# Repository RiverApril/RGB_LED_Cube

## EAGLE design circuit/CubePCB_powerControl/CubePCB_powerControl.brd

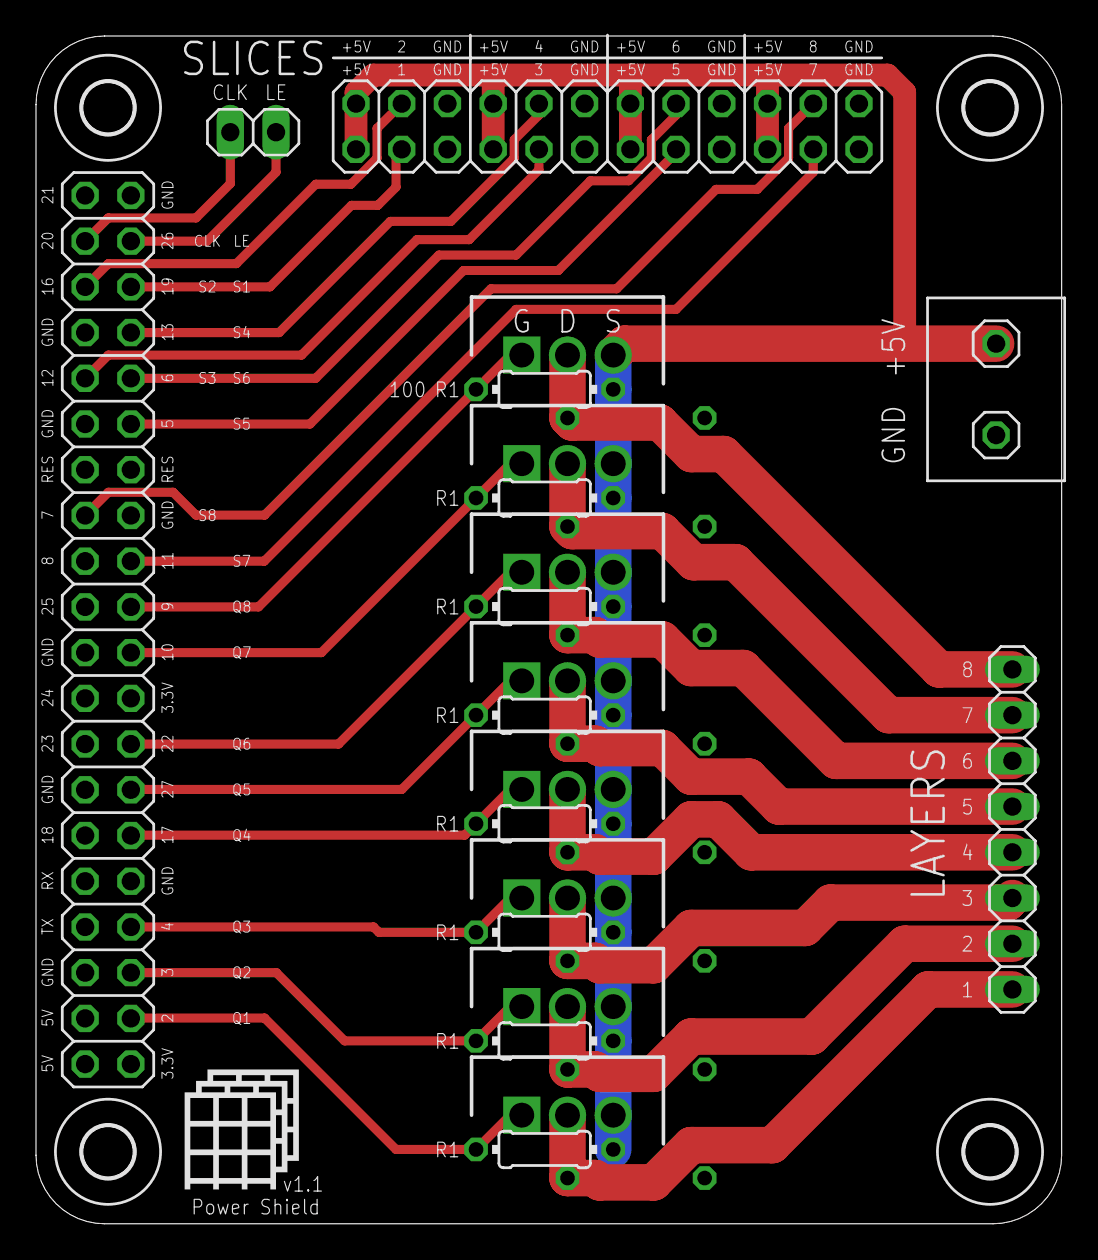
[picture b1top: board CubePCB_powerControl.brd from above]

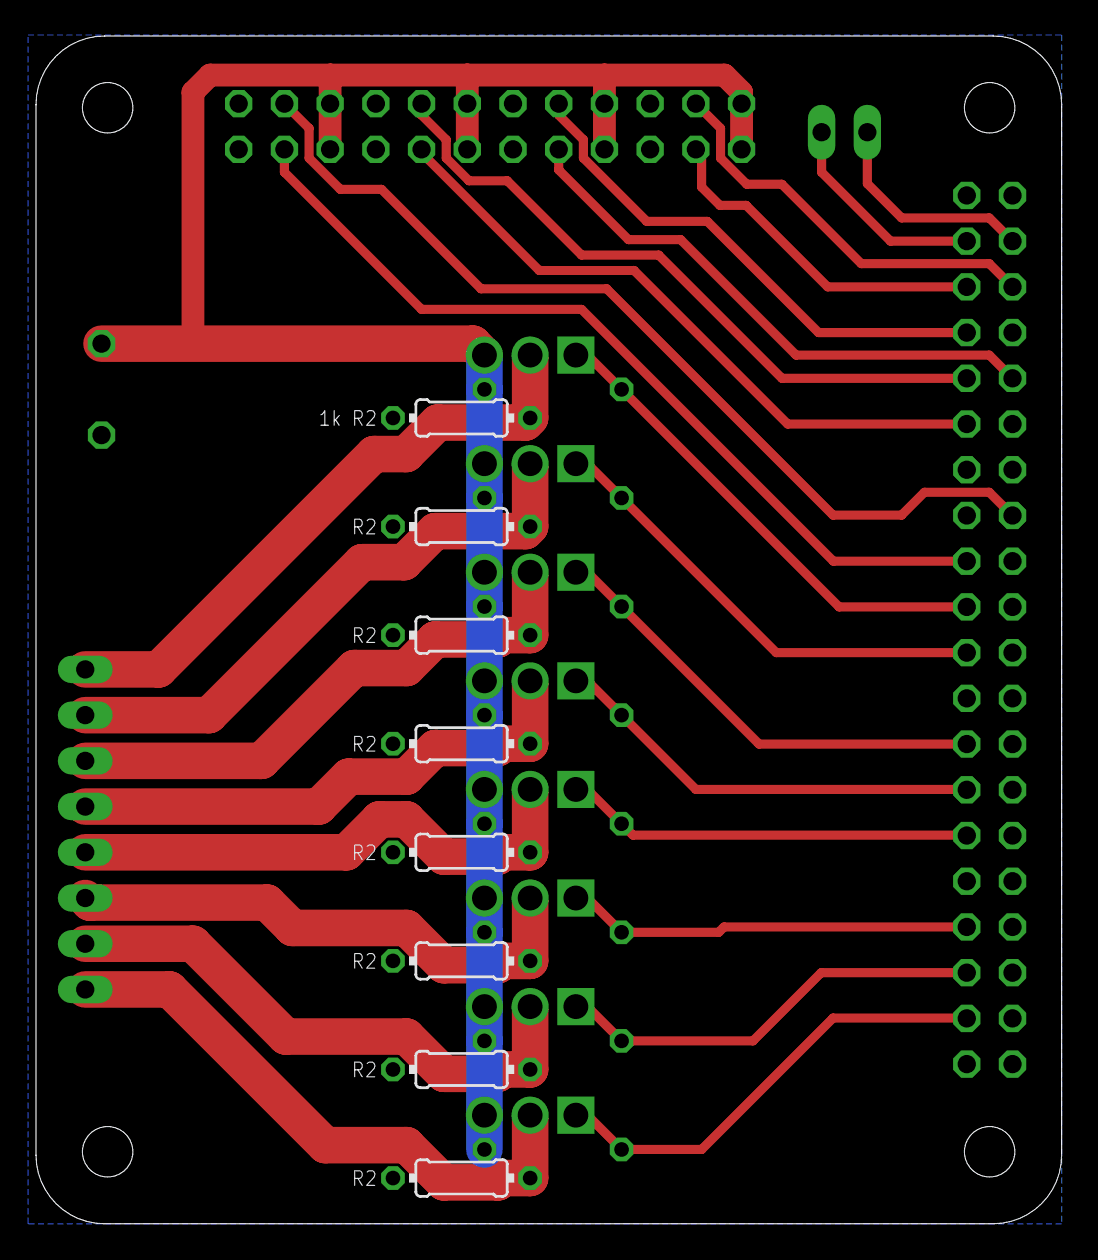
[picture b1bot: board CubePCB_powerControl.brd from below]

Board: 2 copper layers, 57.0 x 66.0 mm, 34 parts (8 on the bottom side), 28 nets.

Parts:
H5, H6, H7, H8: MOUNT-HOLE2.8; 2,8
JP1: 1X08
JP2, JP4: 1X01
JP5: 2X12
JP6: 1X02
LAYER1:Q1, LAYER2:Q1, LAYER3:Q1, LAYER4:Q1, LAYER5:Q1, LAYER6:Q1, LAYER7:Q1, LAYER8:Q1: AUIRF9Z34N; TO254P482X1016X2192-3P
LAYER1:R1, LAYER2:R1, LAYER3:R1, LAYER4:R1, LAYER5:R1, LAYER6:R1, LAYER7:R1, LAYER8:R1: 100; 0204/7
LAYER1:R2, LAYER2:R2, LAYER3:R2, LAYER4:R2, LAYER5:R2, LAYER6:R2, LAYER7:R2, LAYER8:R2: 1k; 0204/7
RASP_PI_GPIO: 2X20

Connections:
+5V: JP4.1, JP5.1, JP5.2, JP5.7, JP5.8, JP5.13, JP5.14, JP5.19, JP5.20, LAYER1:Q1.3, LAYER1:R2.1, LAYER2:Q1.3, LAYER2:R2.1, LAYER3:Q1.3, LAYER3:R2.1, LAYER4:Q1.3, LAYER4:R2.1, LAYER5:Q1.3, LAYER5:R2.1, LAYER6:Q1.3, LAYER6:R2.1, LAYER7:Q1.3, LAYER7:R2.1, LAYER8:Q1.3, LAYER8:R2.1
CLK: JP6.1, RASP_PI_GPIO.38
GND: JP2.1, JP5.5, JP5.6, JP5.11, JP5.12, JP5.17, JP5.18, JP5.23, JP5.24, LAYER1:R1.2, LAYER2:R1.2, LAYER3:R1.2, LAYER4:R1.2, LAYER5:R1.2, LAYER6:R1.2, LAYER7:R1.2, LAYER8:R1.2, RASP_PI_GPIO.9, RASP_PI_GPIO.25, RASP_PI_GPIO.39
L1: JP1.8, LAYER1:Q1.2, LAYER1:R1.1
L2: JP1.7, LAYER2:Q1.2, LAYER2:R1.1
L3: JP1.6, LAYER3:Q1.2, LAYER3:R1.1
L4: JP1.5, LAYER4:Q1.2, LAYER4:R1.1
L5: JP1.4, LAYER5:Q1.2, LAYER5:R1.1
L6: JP1.3, LAYER6:Q1.2, LAYER6:R1.1
L7: JP1.2, LAYER7:Q1.2, LAYER7:R1.1
L8: JP1.1, LAYER8:Q1.2, LAYER8:R1.1
LATCH: JP6.2, RASP_PI_GPIO.37
Q1: LAYER1:Q1.1, LAYER1:R2.2, RASP_PI_GPIO.3
Q2: LAYER2:Q1.1, LAYER2:R2.2, RASP_PI_GPIO.5
Q3: LAYER3:Q1.1, LAYER3:R2.2, RASP_PI_GPIO.7
Q4: LAYER4:Q1.1, LAYER4:R2.2, RASP_PI_GPIO.11
Q5: LAYER5:Q1.1, LAYER5:R2.2, RASP_PI_GPIO.13
Q6: LAYER6:Q1.1, LAYER6:R2.2, RASP_PI_GPIO.15
Q7: LAYER7:Q1.1, LAYER7:R2.2, RASP_PI_GPIO.19
Q8: LAYER8:Q1.1, LAYER8:R2.2, RASP_PI_GPIO.21
S1: JP5.3, RASP_PI_GPIO.35
S2: JP5.4, RASP_PI_GPIO.36
S3: JP5.9, RASP_PI_GPIO.32
S4: JP5.10, RASP_PI_GPIO.33
S5: JP5.15, RASP_PI_GPIO.29
S6: JP5.16, RASP_PI_GPIO.31
S7: JP5.21, RASP_PI_GPIO.23
S8: JP5.22, RASP_PI_GPIO.26

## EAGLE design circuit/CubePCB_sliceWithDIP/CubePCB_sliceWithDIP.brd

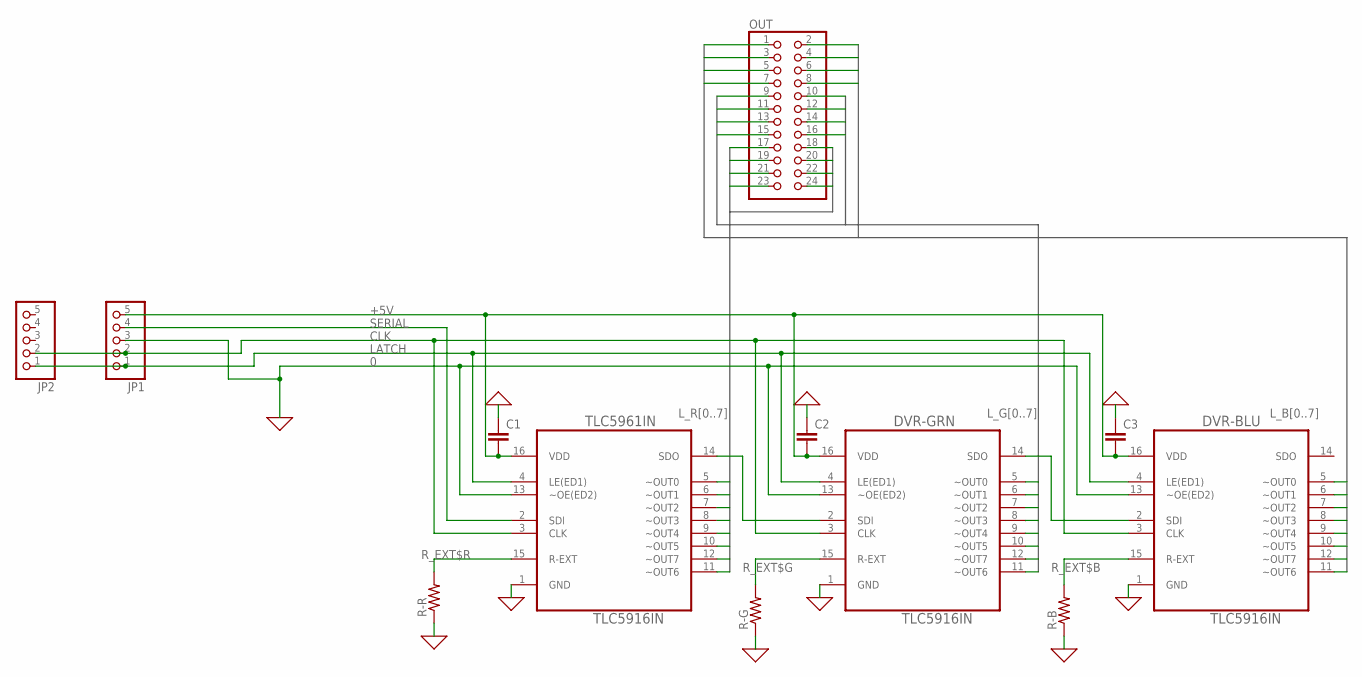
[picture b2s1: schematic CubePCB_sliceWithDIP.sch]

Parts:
C1, C2, C3: C2,5-3; C2.5-3
DVR-BLU: TLC5916IN; DIP254P762X508-16
DVR-GRN: TLC5916IN; DIP254P762X508-16
JP1, JP2: PINHD-1X5; 1X05
OUT: PINHD-2X12; 2X12
R-B: R-US_0204/7; 0204/7
R-G: R-US_0204/7; 0204/7
R-R: R-US_0204/7; 0204/7
TLC5961IN: TLC5916IN; DIP254P762X508-16

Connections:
0: C1.1, C2.1, C3.1, DVR-BLU.1 (GND), DVR-BLU.13 (~OE(ED2)), DVR-GRN.1 (GND), DVR-GRN.13 (~OE(ED2)), JP1.3, R-B.1, R-G.1, R-R.1, TLC5961IN.1 (GND), TLC5961IN.13 (~OE(ED2))
+5V: C1.2, C2.2, C3.2, DVR-BLU.16 (VDD), DVR-GRN.16 (VDD), JP1.5, TLC5961IN.16 (VDD)
CLK: DVR-BLU.3 (CLK), DVR-GRN.3 (CLK), JP1.2, JP2.2, TLC5961IN.3 (CLK)
LATCH: DVR-BLU.4 (LE(ED1)), DVR-GRN.4 (LE(ED1)), JP1.1, JP2.1, TLC5961IN.4 (LE(ED1))
L_B0: DVR-BLU.5 (~OUT0), OUT.7
L_B1: DVR-BLU.6 (~OUT1), OUT.8
L_B2: DVR-BLU.7 (~OUT2), OUT.5
L_B3: DVR-BLU.8 (~OUT3), OUT.6
L_B4: DVR-BLU.9 (~OUT4), OUT.3
L_B5: DVR-BLU.10 (~OUT5), OUT.4
L_B6: DVR-BLU.11 (~OUT6), OUT.1
L_B7: DVR-BLU.12 (~OUT7), OUT.2
L_G0: DVR-GRN.5 (~OUT0), OUT.15
L_G1: DVR-GRN.6 (~OUT1), OUT.16
L_G2: DVR-GRN.7 (~OUT2), OUT.13
L_G3: DVR-GRN.8 (~OUT3), OUT.14
L_G4: DVR-GRN.9 (~OUT4), OUT.11
L_G5: DVR-GRN.10 (~OUT5), OUT.12
L_G6: DVR-GRN.11 (~OUT6), OUT.9
L_G7: DVR-GRN.12 (~OUT7), OUT.10
L_R0: OUT.23, TLC5961IN.5 (~OUT0)
L_R1: OUT.24, TLC5961IN.6 (~OUT1)
L_R2: OUT.21, TLC5961IN.7 (~OUT2)
L_R3: OUT.22, TLC5961IN.8 (~OUT3)
L_R4: OUT.19, TLC5961IN.9 (~OUT4)
L_R5: OUT.20, TLC5961IN.10 (~OUT5)
L_R6: OUT.17, TLC5961IN.11 (~OUT6)
L_R7: OUT.18, TLC5961IN.12 (~OUT7)
unnamed: DVR-GRN.2 (SDI), TLC5961IN.14 (SDO)
unnamed: DVR-BLU.2 (SDI), DVR-GRN.14 (SDO)
R_EXT$B: DVR-BLU.15 (R-EXT), R-B.2
R_EXT$G: DVR-GRN.15 (R-EXT), R-G.2
R_EXT$R: R-R.2, TLC5961IN.15 (R-EXT)
SERIAL: JP1.4, TLC5961IN.2 (SDI)

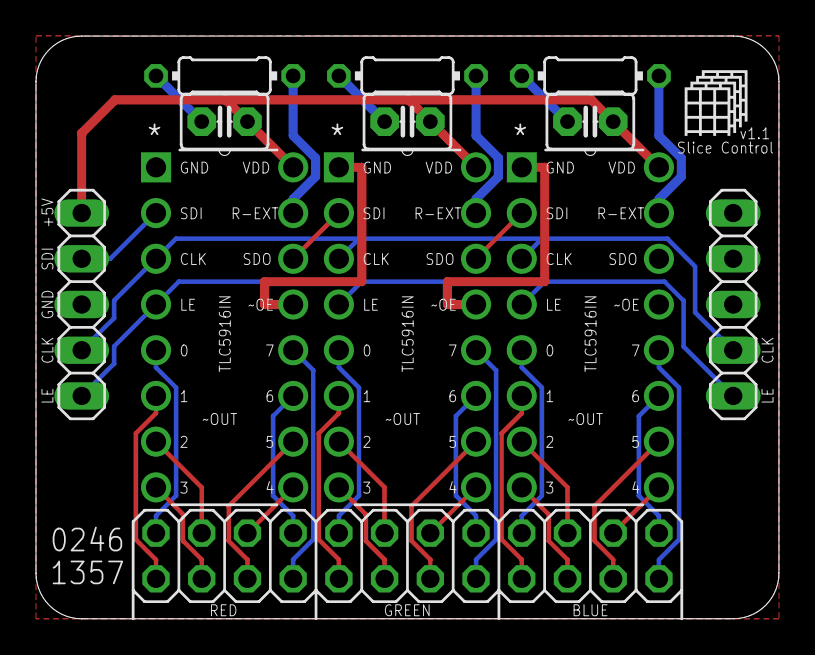
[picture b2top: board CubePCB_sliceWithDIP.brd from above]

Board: 2 copper layers, 41.3 x 32.4 mm, 12 parts (0 on the bottom side), 34 nets.

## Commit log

2018-11-19 init
2018-11-20 added a partly made power control board
2018-12-12 orientation comment
2018-12-12 changed the exit button to HOME
2018-12-12 updated animations
2018-12-12 Added Puzzle Cube Game
2018-12-12 Added connect 4 game
2018-12-12 disabled anim
2018-12-12 updated build for sim
2018-12-14 Added debug game to show axes
2018-12-14 updated slice control board
2018-12-14 added pipes effect
2018-12-15 updated some controls for the puzzle cube
2018-12-15 renamed slice pcb
2018-12-15 brightened up the unselected
2018-12-17 power control board update
2018-12-17 Added 5 pin header
2018-12-17 finalized slice control board
2018-12-18 Continued work on power pcb
2018-12-19 Added traces and silk screen on power board
2018-12-22 Added capacitor
2018-12-23 Added Resistor values
2018-12-23 Removed Shift Register
2018-12-23 Reorganized Traces
2018-12-23 Corrected size of traces
2018-12-23 Adjusted Mosfet spacing
2018-12-30 Fixed outputs 6 and 7
    The scematic part had them out of order so I accidently swapped them.
2019-01-10 Fixed incorrect Mosfet Circuit
2019-01-10 Fixed and added some labels
2019-01-10 Rounded the corners and added more labels to the slice control board
2019-01-25 Fixed resistor labels
2019-01-25 Added a game like the gameshow "Hole in the wall"
2019-01-25 replaced compile files with makefile and reorganized folders
2019-01-25 reduced output from makefile
2019-01-25 lowercase menu
2019-05-14 Started Caves game
2019-05-16 made the Fludd game work
2019-05-16 Added better controller visualization
2019-05-16 changed Pos3 to p3 in core geometry
2019-05-16 changed min and max to be built in versions
2019-05-16 added more ways to cycle menu
2019-05-16 added optimize flag to pi version
2019-05-16 fixed some things for pi
2019-05-19 Renamed to Drop4
2019-05-19 Added LightsOff for safety and externalized sixpair call
2020-03-07 Updated pins for pi
